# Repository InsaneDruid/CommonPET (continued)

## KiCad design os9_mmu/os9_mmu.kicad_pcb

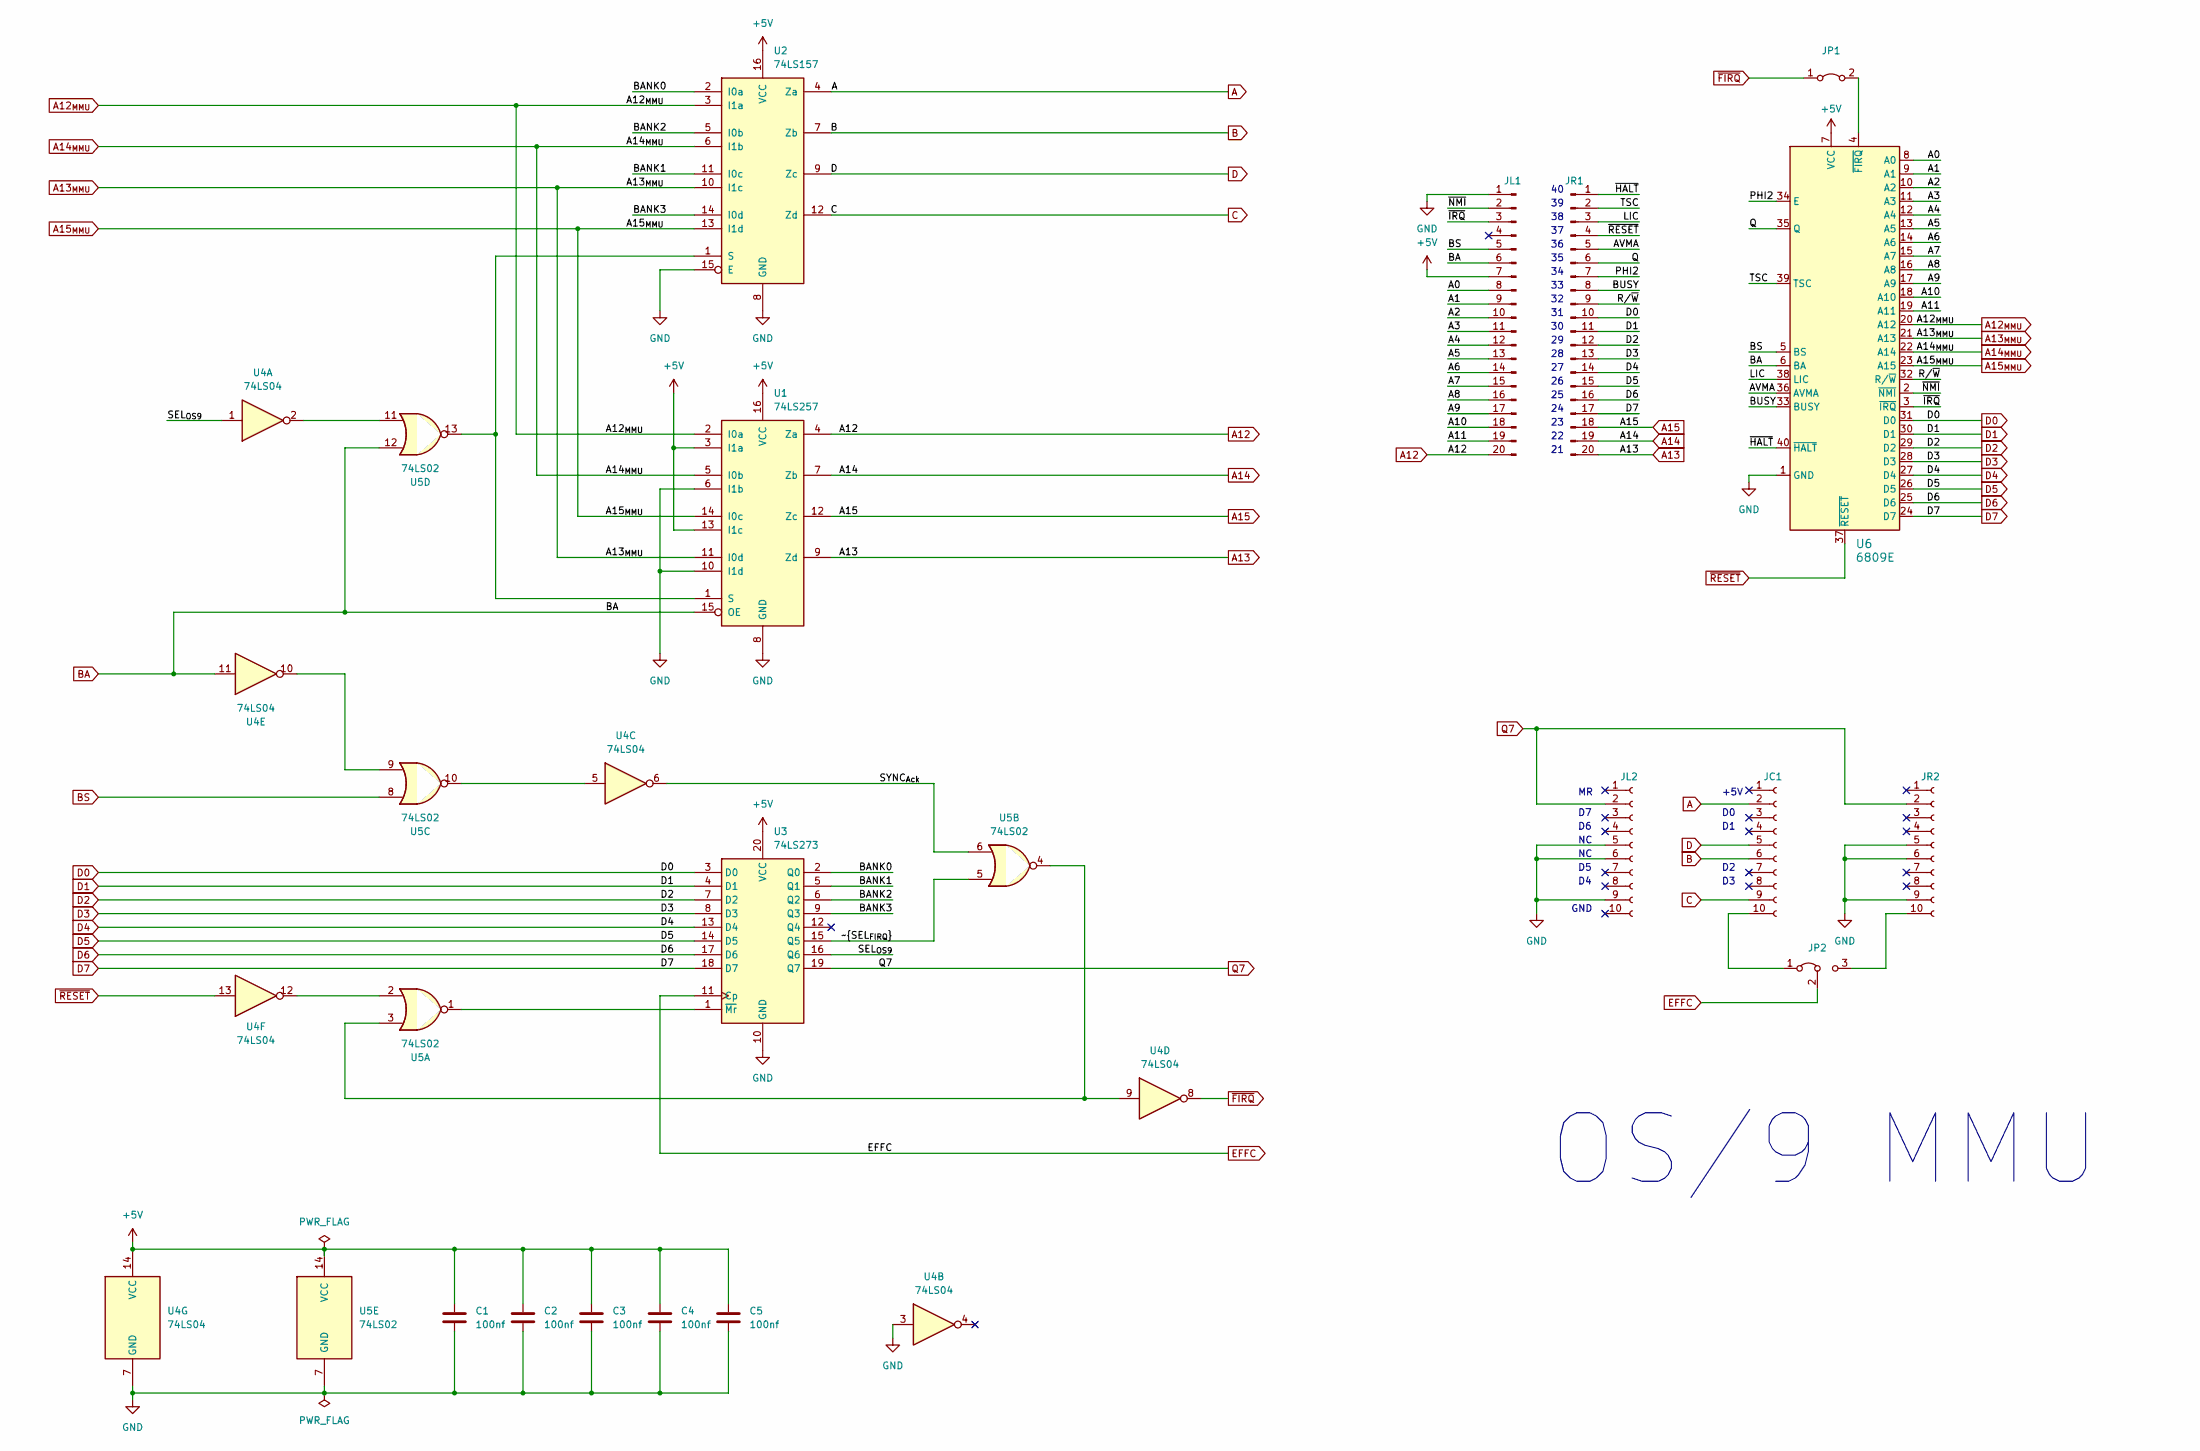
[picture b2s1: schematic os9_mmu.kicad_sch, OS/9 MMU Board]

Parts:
C1, C2, C4, C5: 100nf; C_Disc_D5.0mm_W2.5mm_P2.50mm
C3: 100nf; C_Disc_D5.0mm_W2.5mm_P5.00mm
JC1: Conn_01x10_Pin; PinSocket_1x10_P2.54mm_Vertical
JL1: Conn_01x20_Pin; PinHeader_1x20_P2.54mm_Vertical
JL2: Conn_01x10_Pin; PinSocket_1x10_P2.54mm_Vertical
JP1: Jumper_2_Bridged; PinHeader_1x02_P2.54mm_Vertical
JP2: Jumper_3_Bridged12; PinHeader_1x03_P2.54mm_Vertical
JR1: Conn_01x20_Pin; PinHeader_1x20_P2.54mm_Vertical
JR2: Conn_01x10_Pin; PinSocket_1x10_P2.54mm_Vertical
U1: 74LS257; DIP-16_W7.62mm_LongPads
U2: 74LS157; DIP-16_W7.62mm_LongPads
U3: 74LS273; DIP-20_W7.62mm_LongPads
U4: 74LS04; DIP-14_W7.62mm_LongPads
U5: 74LS02; DIP-14_W7.62mm_LongPads
U6: 6809E; DIP-40_W15.24mm_Socket_LongPads

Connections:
+5V: C1.1, C2.1, C3.1, C4.1, C5.1, JL1.7, U1.3 (I1a), U1.13 (I1c), U1.16 (VCC), U2.16 (VCC), U3.20 (VCC), U4.14 (VCC), U5.14 (VCC), U6.7 (VCC)
/A0: JL1.8, U6.8 (A0)
/A1: JL1.9, U6.9 (A1)
/A2: JL1.10, U6.10 (A2)
/A3: JL1.11, U6.11 (A3)
/A4: JL1.12, U6.12 (A4)
/A5: JL1.13, U6.13 (A5)
/A6: JL1.14, U6.14 (A6)
/A7: JL1.15, U6.15 (A7)
/A8: JL1.16, U6.16 (A8)
/A9: JL1.17, U6.17 (A9)
/A10: JL1.18, U6.18 (A10)
/A11: JL1.19, U6.19 (A11)
/AVMA: JR1.5, U6.36 (AVMA)
/BANK0: U2.2 (I0a), U3.2 (Q0)
/BANK1: U2.11 (I0c), U3.5 (Q1)
/BANK2: U2.5 (I0b), U3.6 (Q2)
/BANK3: U2.14 (I0d), U3.9 (Q3)
/BUSY: JR1.8, U6.33 (BUSY)
/LIC: JR1.3, U6.38 (LIC)
/PHI2: JR1.7, U6.34 (E)
/Q: JR1.6, U6.35 (Q)
/R/~W: JR1.9, U6.32 (R/~W)
/SEL_{OS9}: U3.16 (Q6), U4.1
/SYNC_{Ack}: U4.6, U5.6
/TSC: JR1.2, U6.39 (TSC)
/~HALT: JR1.1, U6.40 (~HALT)
/~IRQ: JL1.3, U6.3 (~IRQ)
/~NMI: JL1.2, U6.2 (~NMI)
/~SEL_{FIRQ}: U3.15 (Q5), U5.5
A: JC1.2, U2.4 (Za)
A12: JL1.20, U1.4 (Za)
A12_{MMU}: U1.2 (I0a), U2.3 (I1a), U6.20 (A12)
A13: JR1.20, U1.9 (Zd)
A13_{MMU}: U1.11 (I0d), U2.10 (I1c), U6.21 (A13)
A14: JR1.19, U1.7 (Zb)
A14_{MMU}: U1.5 (I0b), U2.6 (I1b), U6.22 (A14)
A15: JR1.18, U1.12 (Zc)
A15_{MMU}: U1.14 (I0c), U2.13 (I1d), U6.23 (A15)
B: JC1.6, U2.7 (Zb)
BA: JL1.6, U1.15 (OE), U4.11, U5.12, U6.6 (BA)
BS: JL1.5, U5.8, U6.5 (BS)
C: JC1.9, U2.12 (Zd)
D: JC1.5, U2.9 (Zc)
D0: JR1.10, U3.3 (D0), U6.31 (D0)
D1: JR1.11, U3.4 (D1), U6.30 (D1)
D2: JR1.12, U3.7 (D2), U6.29 (D2)
D3: JR1.13, U3.8 (D3), U6.28 (D3)
D4: JR1.14, U3.13 (D4), U6.27 (D4)
D5: JR1.15, U3.14 (D5), U6.26 (D5)
D6: JR1.16, U3.17 (D6), U6.25 (D6)
D7: JR1.17, U3.18 (D7), U6.24 (D7)
EFFC: JP2.2 (C), U3.11 (Cp)
GND: C1.2, C2.2, C3.2, C4.2, C5.2, JL1.1, JL2.5, JL2.6, JL2.9, JR2.5, JR2.6, JR2.9, U1.6 (I1b), U1.8 (GND), U1.10 (I1d), U2.8 (GND), U2.15 (E), U3.10 (GND), U4.3, U4.7 (GND), U5.7 (GND), U6.1 (GND)
unnamed: JC1.10, JP2.1 (A)
unnamed: JP1.2 (B), U6.4 (~FIRQ)
unnamed: JP2.3 (B), JR2.10
unnamed: U1.1 (S), U2.1 (S), U5.13
unnamed: U3.1 (~Mr), U5.1
unnamed: U4.2, U5.11
unnamed: U4.5, U5.10
unnamed: U4.9, U5.3, U5.4
unnamed: U4.10, U5.9
unnamed: U4.12, U5.2
Q7: JL2.2, JR2.2, U3.19 (Q7)
~FIRQ: JP1.1 (A), U4.8
~RESET: JR1.4, U4.13, U6.37 (~RESET)

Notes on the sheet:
GND
OS/9 MMU
+5V

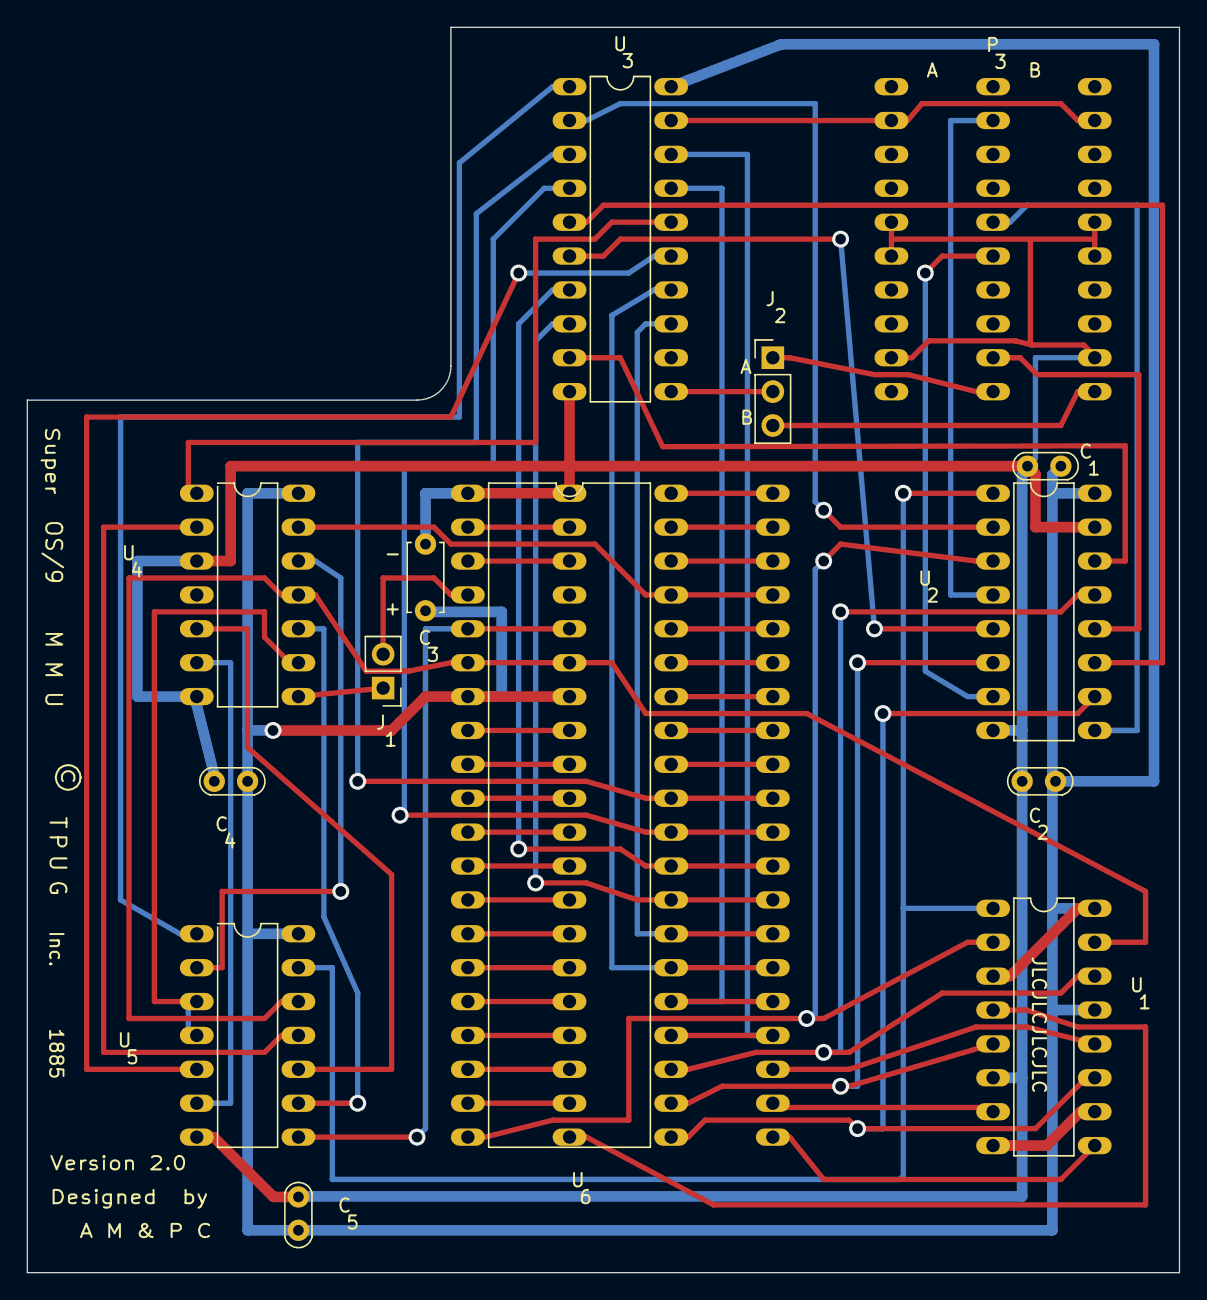
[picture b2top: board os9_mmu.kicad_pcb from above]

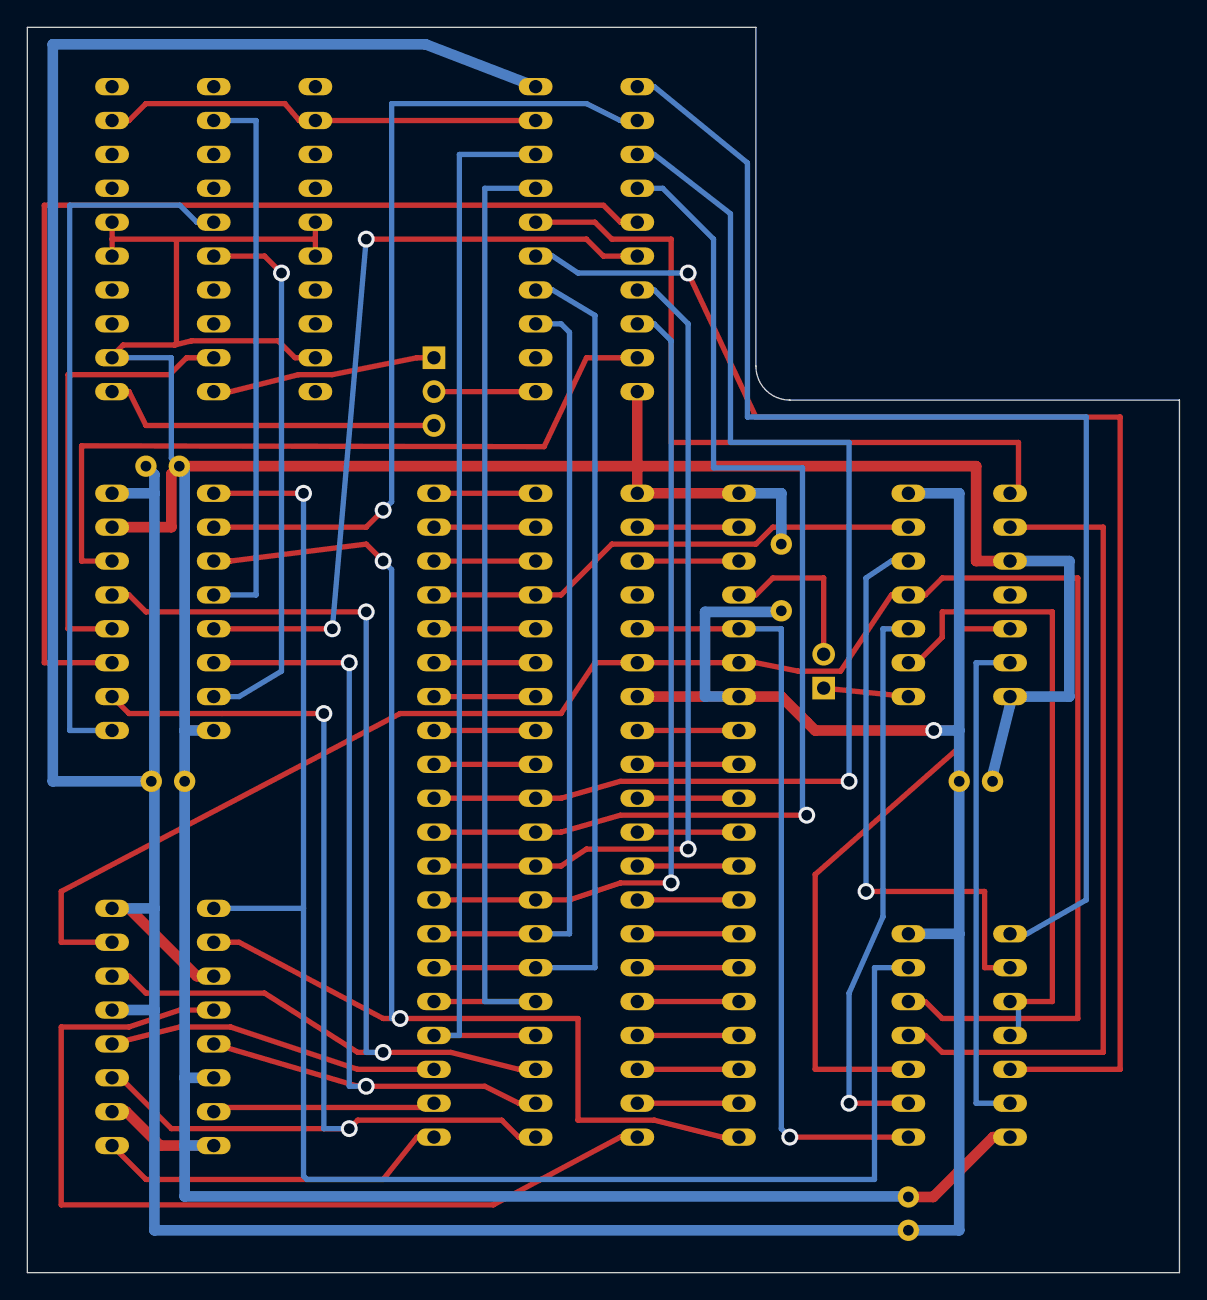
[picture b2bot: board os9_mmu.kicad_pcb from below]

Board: 2 copper layers, 86.4 x 93.3 mm, 18 parts (2 on the bottom side), 67 nets.

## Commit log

2023-07-18 added MMU readme file
2023-07-18 changed size for readme images
2023-10-30 Added traces and netlist to BOM
    - the BOM now contains the graphical representation of all traces and nets
2023-10-30 Cosmetic datasheet fixes
    - fixed position of U35 designator to not be overlapping that of Q5
    - added proper links to datasheets of 74LS393
2024-02-16 MMU adjustments
    -adjusted power trace widths
    -reintroduced solder mask layer - was absence to give board a vintage look but makes silkscreen prints impossible
    -fixed license links in drawing sheets to match board prints, readme and project
2024-02-16 kicad drawing sheet fixes
    fixed license links in drawing sheets to match board prints, readme and project
